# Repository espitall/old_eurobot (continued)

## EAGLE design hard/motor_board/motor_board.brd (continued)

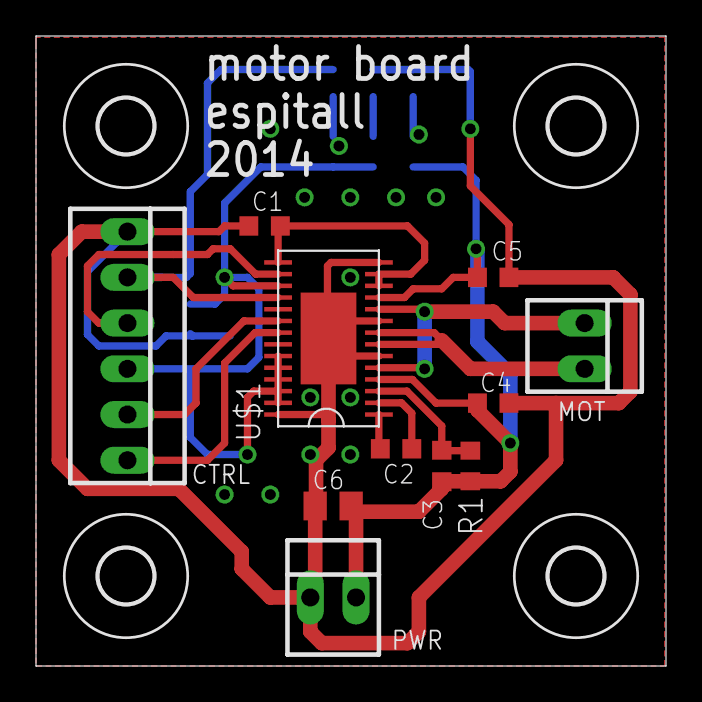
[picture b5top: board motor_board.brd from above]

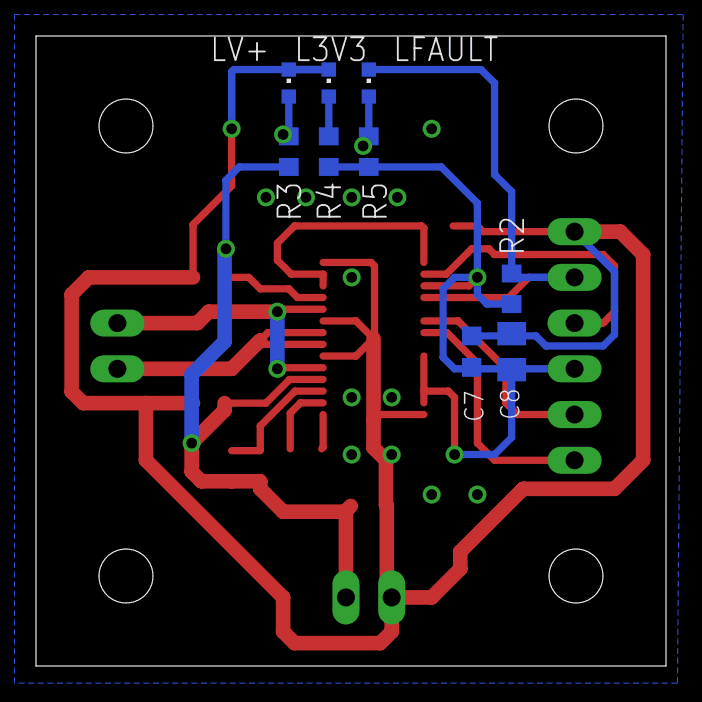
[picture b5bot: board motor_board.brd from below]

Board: 2 copper layers, 35.0 x 35.0 mm, 24 parts (9 on the bottom side), 16 nets.

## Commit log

2014-06-04 initial import
2014-06-04 Creation d'une tache par interface
2014-06-04 Creation d'un repertoire pour le code du robot principal
2014-06-04 Corrige bug de compilation
2014-06-04 debut de gestion des moteurs
2014-06-04 fichiers manquants
2014-06-04 amélioration de la com
2014-06-04 gestion de la com
2014-06-05 ajout de l'interface de control
2014-06-05 gestion de l'ordre reset dans la com
2014-06-06 gestion de l'ouverture du port SPI
2014-06-06 gestion de la SPI en lecture
2014-06-06 gestion des deux codeurs
2014-06-07 refactor du code de l'ui
2014-06-07 debut de l'asserv avec graph
2014-06-07 PID angle avec graph
2014-06-07 ajout de params sur les graphs d'asserv
2014-06-08 ajout des graphes pour les rampes
2014-06-08 lecture des params d'asserv
2014-06-09 ecriture des params d'asserv
2014-06-09 ajout de donnees sur les graphes
2014-06-09 amelioration de l'information sur le reset
2014-06-11 gestion de la rampe de vitesse en distance
2014-06-12 Affichage des donnes d'asserv dans le bon onglet uniquement
2014-07-03 design de la carte moteur
2014-07-03 gestion stm32
2014-07-04 carte de support pour le gyro
2014-09-05 mise a jour depot
2014-09-05 FreeRTOS sur stm32f4
2014-09-08 gestion de chibios + lcd
2014-09-08 remove ugfx
2014-09-08 vérification des arguments des printf-like
2014-09-09 changement du nom 2014 -> 2015
2014-09-09 gestion de la SDRAM
2014-09-09 correction sur la gestion de la sdram
2014-11-01 fichiers manquants + petit menage
2014-11-08 gestion d'un moteur pour carte avec pinout corrigé
2014-11-08 suppression fichier temporaire
2014-11-08 gestion du moteur 2
2014-11-08 test de gestion d'un encodeur avec pining corrigé
2014-11-08 module de positionnement basique pour test de la carte
2014-11-08 correction bug affichage sur la console
2014-11-08 empeche un buffer overflow en cas d'utilisation de carateres ASCII etendu
2014-11-09 re-affectation pin
2014-11-09 test sur deux moteurs
2014-11-09 test 2 codeurs
2014-11-09 rotation de 180° de l'ecran
2014-11-19 code pour la demo au L@bx
2014-11-21 test commit
2014-11-21 test de commit
2014-12-05 Nettoyage
2014-12-05 reaffectation pin de la carte interface
2014-12-05 Début d'implémentation pour l'ADC
2014-12-07 Gestion des 2 canaux pour l'ADC
2014-12-19 renomage adc => max11628
2014-12-19 renomage constante ADC_REFERENCE_VOLTAGE => MAX66128_REFERENCE_VOLTAGE
2014-12-19 Ajout code pour tester max11628 Modif Makefile pour inclure le max11628
2014-12-19 gestion module pwm (pca9685)
2014-12-19 test max11628
2014-12-27 carte interface
2014-12-27 schema de la carte usir (UltraSonic - InfraRed)
2014-12-27 routage USIR
2014-12-28 labels manquants
2015-01-16 debug module max11628
2015-02-08 test des périphrériques sur la nouvelle version de la carte
2015-02-13 carte actionneur pour robot principal
2015-02-14 création d'un répertoire pour le deuxième robot
2015-02-14 test des moteurs du robot secondaire
2015-02-14 debut de gestion atxmega16a4 dans Chibios pour test carte USIR
2015-02-14 gestion de la carte USIR sous ChibiOS
2015-02-15 Changement des Makefile pour faciliter l'ajout de modules
2015-02-15 test du hard pour la com inter cartes
2015-02-27 test dc_motor
2015-02-27 tests
2015-02-27 debut de code pour gyro
2015-02-27 test
2015-03-13 Implémentation du gyro
2015-03-19 commit avant merge
2015-03-20 possibilité de désactivé l'asserv
2015-03-20 paramétrage de l'asserv
2015-03-21 debut du gestionnaire de trajectoire
2015-03-21 test module trajectoire sans mouvement (temporisation uniquement)
2015-03-21 main.c
2015-03-21 implementation du goto_a
2015-03-27 travail sur trajectory + test servo + squelette pathfinder
2015-03-28 correction sur l'ordonnanceur xmega, correction sur la com spi
2015-03-28 gestion evsys sur xmega pour US
2015-03-31 Début d'implémentation du pathfinder Début de la création d'un simulateur
2015-04-01 Séparation du code du simulateur dans différent dossier
2015-04-01 Représentation du terrain et des éléments pour le simulateur
2015-04-03 Gestion de la matrice des obstacles
2015-04-04 carré sur table au labx
2015-04-04 Renommage des fonctions dans le simulateur
2015-04-05 activation des ADC pour capteurs IR
2015-04-05 gestion couleur dans la console
2015-04-05 gestion detection erreur sur USIR
2015-04-05 gestion des IO
2015-04-05 gestion des couleurs pour l'affichage batterie
2015-04-06 calage dans la zone de depart
2015-04-06 Mise au propre et deboguage du simulateur
2015-04-08 reprise du code pour l'affichage de la carte
2015-04-08 Ajout de directives au préprocesseur
2015-04-08 fix problème avec les directives du préprocesseur
2015-04-09 Pathfinder : On teste tout de suite si la destination est une zone accessible
2015-04-09 Pathfinder : Affichage des calcules de distances des voisins en diagonal
2015-04-09 Simulateur : Choix du robot secondaire par defaut sinon il bloque la route
2015-04-09 fix astar et implementation des differentes heuristiques
2015-04-10 Ajout de malus en cas de changement de trajectoire
2015-04-11 poster 2015
2015-04-11 deboguage astar en cours
2015-04-12 deboguage astar (suite)
2015-04-12 Déplacement de toutes les constantes du simulateur dans config.h
2015-04-16 simulateur : reglage debug et parametrage
2015-04-17 ajout de trace de debug
2015-04-21 Simulateur : Ajout des zones de danger
2015-04-21 Simlateur : Prise du malus de terrain
2015-04-22 simulateur : fix bug malus terrain
2015-04-22 Simulateur : deplacement d'une variable globale du .h au .c
2015-04-23 Simulateur : fix bugs
2015-04-24 Simulateur : implémentation de l'algo Dijkstra
2015-04-24 Affichage des checkpoints
2015-04-24 gestion du calage + debut usir/step
2015-04-24 affinage des zones et parametrages
2015-04-28 Initialisation de la carte pour le pathfinder
2015-04-30 Implémentation du pathfinder
2015-05-01 fix pathfinder
2015-05-01 pathfinder : suppression du point start + ajout de traces de debug
2015-05-01 plein de choses que j'aurais du commit plus tot....
2015-05-01 fix appel lcdPrintln suite au merge
2015-05-01 parametrage simulateur idem parametrage carte
2015-05-07 fix poster
2015-05-07 test pmi
2015-05-10 travail sur PMI
2015-05-11 travail de dimanche pour prendre des spots
2015-05-11 correction taille poster
2015-05-13 Ajout d'une deuxième zone de danger Ajout de la possibilité d'avoir une résolution différente pour l'affichage du simulateur que celle de la carte Paramètrage Tests
2015-05-13 Ajout d'une deuxième zone de danger Création des cartes pour les 2 robots manuellement Distinction des 2 robots Tests
2015-05-13 code homologation
2015-05-13 Fix carte pour robot secondaire Ajout des cartes faites manuellement également dans le simulateur Tests du simulateurs
2015-05-15 code pre-match 3
